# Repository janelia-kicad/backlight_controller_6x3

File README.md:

- [Repository Information](#org89e2f96)
  - [Description](#org01946da)
- [Images](#org5e6b005)
- [Schematic](#org50048ed)
- [Gerbers](#org1f83db4)
- [Bill of Materials](#org4e1d2f2)
  - [PCB Parts](#org0365191)
  - [Supplemental Parts](#org1217ce1)
  - [Vendor Parts Lists](#orge2d2bad)
- [Supplemental Documentation](#org1794ae5)
  - [Assembly Instructions](#orgcad51c4)
- [Manufacturing Archive](#orgdf269ab)

# Repository Information

-   **Name:** backlight\_controller\_6x3
-   **Version:** 1.0
-   **License:** Open-Source Hardware
-   **URL:** <https://github.com/janelia-kicad/backlight_controller_6x3>
-   **Author:** Peter Polidoro
-   **Email:** peter@polidoro.io

## Description

This board controls up to four Smart Vision backlights with IR and visible channels plus additional high and low power channel outputs.

# Images

# Schematic

[./schematic/backlight\_controller\_6x3.pdf](./schematic/backlight_controller_6x3.pdf)

# Gerbers

# Bill of Materials

## PCB Parts

| Item | Reference(s)                                                | Quantity | Manufacturer Part Number | Description                                                       |
|---- |----------------------------------------------------------- |-------- |------------------------ |----------------------------------------------------------------- |
| 1    | C1 C2                                                       | 2        | C2012X5R1V106M085AC      | CAP CER 10UF 35V X5R                                              |
| 2    | C3 C4 C5 C6 C7 C8 C9                                        | 7        | C0805T104K5RAL7800       | CAP CER 0.1UF 50V X7R                                             |
| 3    | D1 D10 D11 D12 D13 D14 D15 D16 D17 D2 D3 D4 D5 D6 D7 D8 D9  | 17       | LTST-C170GKT             | LED GREEN CLEAR SMD                                               |
| 4    | HPS1 HPS2 HPS3 HPS4                                         | 4        | BTS3256DAUMA1            | IC SWITCH SMART LOWSIDE                                           |
| 5    | J1                                                          | 1        | 09551156612741           | CONN D-SUB RCPT 9POS SMD SOLDER                                   |
| 6    | J10 J3 J4 J5 J6 J7 J8 J9                                    | 8        | 1411976                  | CONN FMALE INSERT 5POS SOLDER                                     |
| 7    | J2                                                          | 1        | 09551296812741           | CONN D-SUB PLUG 9POS SMD SOLDER                                   |
| 8    | P1                                                          | 1        | 0039301060               | CONN HEADER 6POS 4.2MM R/A TIN                                    |
| 9    | R1                                                          | 1        | ERJ-6ENF2201V            | RES SMD 2.2K OHM 1% 1/8W                                          |
| 10   | R10 R2 R4 R6 R8                                             | 5        | ERJ-6ENF5901V            | RES SMD 5.9K OHM 1% 1/8W                                          |
| 11   | R11 R13 R15 R17 R19 R20 R21 R22 R23 R24 R25 R26 R3 R5 R7 R9 | 16       | ERJ-6ENF2870V            | RES SMD 287 OHM 1% 1/8W                                           |
| 12   | R12 R14 R16 R18                                             | 4        | ERJ-6ENF75R0V            | RES SMD 75 OHM 1% 1/8W                                            |
| 13   | REG1                                                        | 1        | R-78C5.0-1.0             | CONV DC/DC 1A 5V OUT SIP VERT                                     |
| 14   | SW1 SW2                                                     | 2        | KT11P4SM34LFS            | SWITCH TACTILE SPST-NO 1VA 32V                                    |
| 15   | TEENSY1                                                     | 1        | DEV-14056                | TEENSY 3.5 HDRS K64 EVAL BRD                                      |
| 16   | U1 U2                                                       | 2        | SN74ABT541BDWR           | Buffer Non-Inverting 1 Element 8 Bit per Element Push-Pull Output |
| 17   | U10 U11 U3 U4 U5 U6 U7 U8 U9                                | 9        | NUD3124LT1G              | IC INDCT LOAD DRVR AUTO                                           |
| 18   | U12                                                         | 1        | MAX6817EUT+T             | IC DEBOUNCER SWITCH DUAL                                          |

## Supplemental Parts

| Item | Quantity | Manufacturer Part Number   | Description                    |
|---- |-------- |-------------------------- |------------------------------ |
| 1    | 1        | GST280A24-C6P              | AC/DC DESKTOP ADAPTER 24V 280W |
| 2    | 1        | CORD IEC 320-C13 6FT BLACK | CORD IEC 320-C13 6FT BLACK     |

## Vendor Parts Lists

[./bom/Digi-Key\_parts.csv](./bom/Digi-Key_parts.csv)

[./bom/supplemental\_Digi-Key\_parts.csv](./bom/supplemental_Digi-Key_parts.csv)

# Supplemental Documentation

## Assembly Instructions

-   Solder surface mount and through hole components onto the pcb.

# Manufacturing Archive

Send manufacturing zip file to your favorite PCB manufacturer for fabrication.

[./manufacturing/backlight\_controller\_6x3\_v1.0.zip](./manufacturing/backlight_controller_6x3_v1.0.zip)

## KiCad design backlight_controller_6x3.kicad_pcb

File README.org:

# Created 2019-06-07 Fri 10:33
#+OPTIONS: title:nil author:nil email:nil toc:t |:t ^:nil
* Repository Information

- Name :: backlight_controller_6x3
- Version :: 1.0
- License :: Open-Source Hardware
- URL :: https://github.com/janelia-kicad/backlight_controller_6x3
- Author :: Peter Polidoro
- Email :: peter@polidoro.io

** Description

This board controls up to four Smart Vision backlights with IR and visible
channels plus additional high and low power channel outputs.

* Images

* Schematic

[[file:./schematic/backlight_controller_6x3.pdf][./schematic/backlight_controller_6x3.pdf]]

[[file:./schematic/images/schematic00.png]]

[[file:./schematic/images/schematic01.png]]

[[file:./schematic/images/schematic02.png]]

[[file:./schematic/images/schematic03.png]]

[[file:./schematic/images/schematic04.png]]

[[file:./schematic/images/schematic05.png]]

[[file:./schematic/images/schematic06.png]]

[[file:./schematic/images/schematic07.png]]

[[file:./schematic/images/schematic08.png]]

[[file:./schematic/images/schematic09.png]]

[[file:./schematic/images/schematic10.png]]

[[file:./schematic/images/schematic11.png]]

[[file:./schematic/images/schematic12.png]]

[[file:./schematic/images/schematic13.png]]

[[file:./schematic/images/schematic14.png]]

[[file:./schematic/images/schematic15.png]]

[[file:./schematic/images/schematic16.png]]

[[file:./schematic/images/schematic17.png]]

[[file:./schematic/images/schematic18.png]]

[[file:./schematic/images/schematic19.png]]

[[file:./schematic/images/schematic20.png]]

[[file:./schematic/images/schematic21.png]]

* Gerbers

[[file:./gerbers/images/gerbers00.png]]

[[file:./gerbers/images/gerbers01.png]]

* Bill of Materials

** PCB Parts

| Item | Reference(s)                                                | Quantity | Manufacturer Part Number | Description                                                       |
|------+-------------------------------------------------------------+----------+--------------------------+-------------------------------------------------------------------|
|    1 | C1 C2                                                       |        2 | C2012X5R1V106M085AC      | CAP CER 10UF 35V X5R                                              |
|    2 | C3 C4 C5 C6 C7 C8 C9                                        |        7 | C0805T104K5RAL7800       | CAP CER 0.1UF 50V X7R                                             |
|    3 | D1 D10 D11 D12 D13 D14 D15 D16 D17 D2 D3 D4 D5 D6 D7 D8 D9  |       17 | LTST-C170GKT             | LED GREEN CLEAR SMD                                               |
|    4 | HPS1 HPS2 HPS3 HPS4                                         |        4 | BTS3256DAUMA1            | IC SWITCH SMART LOWSIDE                                           |
|    5 | J1                                                          |        1 | 09551156612741           | CONN D-SUB RCPT 9POS SMD SOLDER                                   |
|    6 | J10 J3 J4 J5 J6 J7 J8 J9                                    |        8 | 1411976                  | CONN FMALE INSERT 5POS SOLDER                                     |
|    7 | J2                                                          |        1 | 09551296812741           | CONN D-SUB PLUG 9POS SMD SOLDER                                   |
|    8 | P1                                                          |        1 | 0039301060               | CONN HEADER 6POS 4.2MM R/A TIN                                    |
|    9 | R1                                                          |        1 | ERJ-6ENF2201V            | RES SMD 2.2K OHM 1% 1/8W                                          |
|   10 | R10 R2 R4 R6 R8                                             |        5 | ERJ-6ENF5901V            | RES SMD 5.9K OHM 1% 1/8W                                          |
|   11 | R11 R13 R15 R17 R19 R20 R21 R22 R23 R24 R25 R26 R3 R5 R7 R9 |       16 | ERJ-6ENF2870V            | RES SMD 287 OHM 1% 1/8W                                           |
|   12 | R12 R14 R16 R18                                             |        4 | ERJ-6ENF75R0V            | RES SMD 75 OHM 1% 1/8W                                            |
|   13 | REG1                                                        |        1 | R-78C5.0-1.0             | CONV DC/DC 1A 5V OUT SIP VERT                                     |
|   14 | SW1 SW2                                                     |        2 | KT11P4SM34LFS            | SWITCH TACTILE SPST-NO 1VA 32V                                    |
|   15 | TEENSY1                                                     |        1 | DEV-14056                | TEENSY 3.5 HDRS K64 EVAL BRD                                      |
|   16 | U1 U2                                                       |        2 | SN74ABT541BDWR           | Buffer Non-Inverting 1 Element 8 Bit per Element Push-Pull Output |
|   17 | U10 U11 U3 U4 U5 U6 U7 U8 U9                                |        9 | NUD3124LT1G              | IC INDCT LOAD DRVR AUTO                                           |
|   18 | U12                                                         |        1 | MAX6817EUT+T             | IC DEBOUNCER SWITCH DUAL                                          |

** Supplemental Parts

| Item | Quantity | Manufacturer Part Number   | Description                    |
|------+----------+----------------------------+--------------------------------|
|    1 |        1 | GST280A24-C6P              | AC/DC DESKTOP ADAPTER 24V 280W |
|    2 |        1 | CORD IEC 320-C13 6FT BLACK | CORD IEC 320-C13 6FT BLACK     |

** Vendor Parts Lists

[[file:./bom/Digi-Key_parts.csv][./bom/Digi-Key_parts.csv]]

[[file:./bom/supplemental_Digi-Key_parts.csv][./bom/supplemental_Digi-Key_parts.csv]]

* Supplemental Documentation

** Assembly Instructions

- Solder surface mount and through hole components onto the pcb.

* Manufacturing Archive

Send manufacturing zip file to your favorite PCB manufacturer for fabrication.

[[file:./manufacturing/backlight_controller_6x3_v1.0.zip][./manufacturing/backlight_controller_6x3_v1.0.zip]]

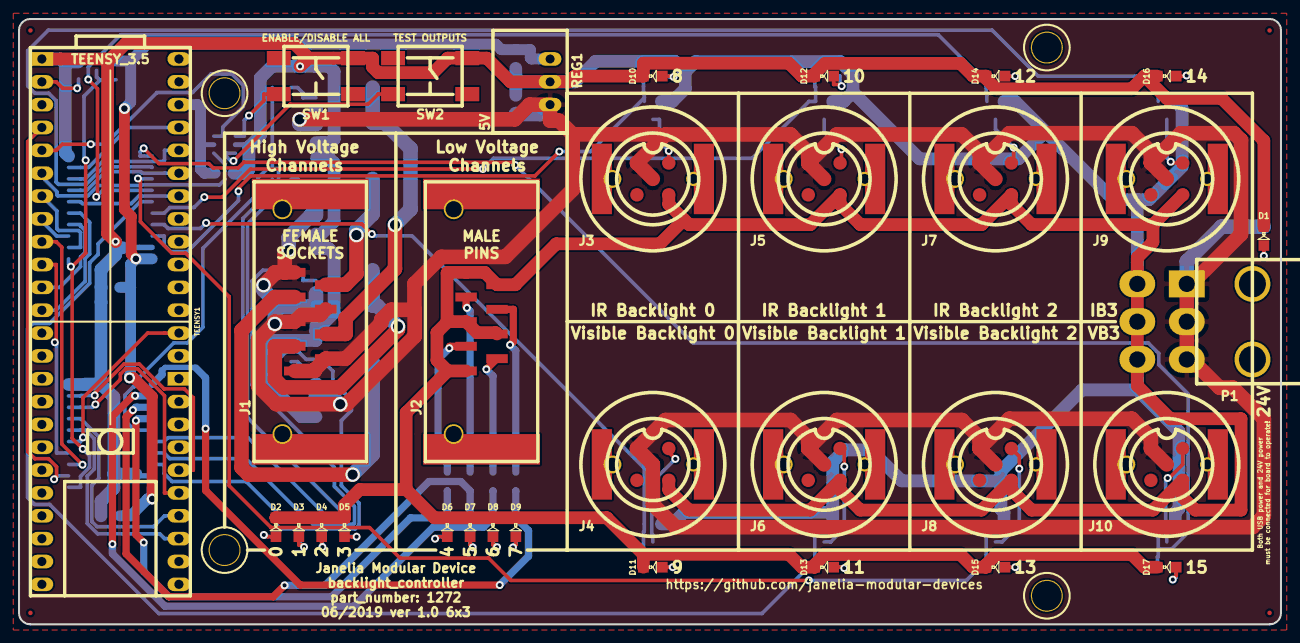
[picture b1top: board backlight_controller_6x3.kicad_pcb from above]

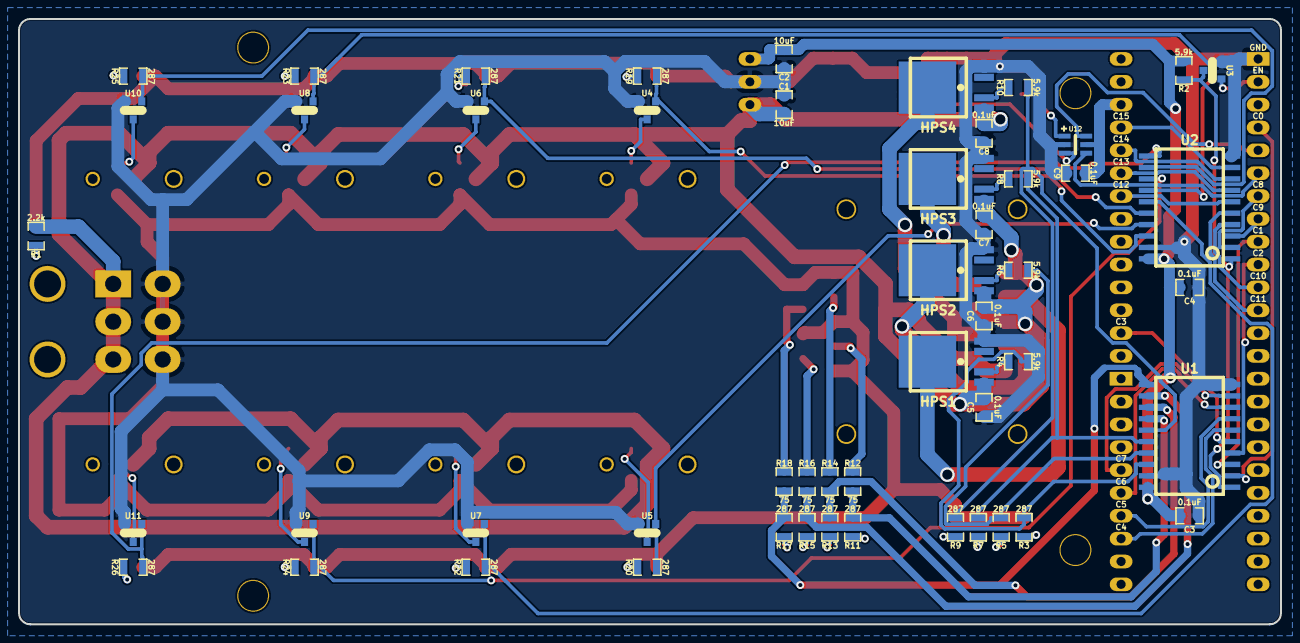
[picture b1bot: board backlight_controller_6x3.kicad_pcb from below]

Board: 2 copper layers, 140.3 x 67.3 mm, 91 parts (51 on the bottom side), 79 nets.

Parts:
C1, C2: 10uF; SM0805
C3, C4, C5, C6, C7, C8, C9: 0.1uF; SM0805
D1, D2, D3, D4, D5, D6, D7, D8, D9, D10, D11, D12, D13, D14, D15, D16, D17: LED_GRN; LED0805
FID1, FID2, FID3, FID4: FIDUCIAL
HPS1, HPS2, HPS3, HPS4: BTS3256; PG-TO252-5-11
J1: DB9F; DB9F_SMD
J2: DB9M; DB9M_SMD
J3, J4, J5, J6, J7, J8, J9, J10: M12-5-RCPT; M12-5_RCPT_F_SMD
MH1, MH2, MH3, MH4: MOUNTING_HOLE_4-40
P1: MINI_FIT; MINI-FIT-JR_02X03_M_RA
R1: 2.2k; SM0805
R2, R4, R6, R8, R10: 5.9k; SM0805
R3, R5, R7, R9, R11, R13, R15, R17, R19, R20, R21, R22, R23, R24, R25, R26: 287; SM0805
R12, R14, R16, R18: 75; SM0805
REG1: CONV_DC_DC_5V_1A; DC_DC_CONV_R78C
SW1, SW2: VAL**; SWITCH_KT
TEENSY1: TEENSY_3.5; TEENSY_3.5_MIN
U1, U2: SN74ABT541BDWR; SOIC_20
U3, U4, U5, U6, U7, U8, U9, U10, U11: NUD3124; TO-236-3
U12: VAL**; MAX6817

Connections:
+3V3: C9.1, TEENSY1.3V3, U12.5
/CHANNEL_0: TEENSY1.2, U1.2
/CHANNEL_1: TEENSY1.7, U1.3
/CHANNEL_2: TEENSY1.8, U1.4
/CHANNEL_3: TEENSY1.14, U1.5
/CHANNEL_4: TEENSY1.35, U1.6
/CHANNEL_5: TEENSY1.36, U1.7
/CHANNEL_6: TEENSY1.37, U1.8
/CHANNEL_7: TEENSY1.38, U1.9
/CHANNEL_8: TEENSY1.5, U2.2
/CHANNEL_9: TEENSY1.6, U2.3
/CHANNEL_10: TEENSY1.9, U2.4
/CHANNEL_11: TEENSY1.10, U2.5
/CHANNEL_12: TEENSY1.20, U2.6
/CHANNEL_13: TEENSY1.21, U2.7
/CHANNEL_14: TEENSY1.22, U2.8
/CHANNEL_15: TEENSY1.23, U2.9
/ENABLE: TEENSY1.0, U3.1
/backlight_6x3/C_0: R3.1, R4.1, U1.18
/backlight_6x3/C_1: R5.1, R6.1, U1.17
/backlight_6x3/C_2: R7.1, R8.1, U1.16
/backlight_6x3/C_3: R9.1, R10.1, U1.15
/backlight_6x3/C_4: R11.1, R12.1, U1.14
/backlight_6x3/C_5: R13.1, R14.1, U1.13
/backlight_6x3/C_6: R15.1, R16.1, U1.12
/backlight_6x3/C_7: R17.1, R18.1, U1.11
/backlight_6x3/C_8: R19.1, U2.18, U4.1
/backlight_6x3/C_9: R20.1, U2.17, U5.1
/backlight_6x3/C_10: R21.1, U2.16, U6.1
/backlight_6x3/C_11: R22.1, U2.15, U7.1
/backlight_6x3/C_12: R23.1, U2.14, U8.1
/backlight_6x3/C_13: R24.1, U2.13, U9.1
/backlight_6x3/C_14: R25.1, U2.12, U10.1
/backlight_6x3/C_15: R26.1, U2.11, U11.1
/backlight_6x3/backlight_outputs/ir_0/NPN: J3.2, U4.3
/backlight_6x3/backlight_outputs/ir_1/NPN: J5.2, U6.3
/backlight_6x3/backlight_outputs/ir_2/NPN: J7.2, U8.3
/backlight_6x3/backlight_outputs/ir_3/NPN: J9.2, U10.3
/backlight_6x3/backlight_outputs/visible_0/NPN: J4.2, U5.3
/backlight_6x3/backlight_outputs/visible_1/NPN: J6.2, U7.3
/backlight_6x3/backlight_outputs/visible_2/NPN: J8.2, U9.3
/backlight_6x3/backlight_outputs/visible_3/NPN: J10.2, U11.3
/backlight_6x3/high_voltage_outputs/OUTPUT_0: HPS1.6, J1.2
/backlight_6x3/high_voltage_outputs/OUTPUT_1: HPS2.6, J1.4
/backlight_6x3/high_voltage_outputs/OUTPUT_2: HPS3.6, J1.6
/backlight_6x3/high_voltage_outputs/OUTPUT_3: HPS4.6, J1.8
/backlight_6x3/high_voltage_outputs/high_voltage_output_0/FAULT: HPS1.2, R4.2
/backlight_6x3/high_voltage_outputs/high_voltage_output_1/FAULT: HPS2.2, R6.2
/backlight_6x3/high_voltage_outputs/high_voltage_output_2/FAULT: HPS3.2, R8.2
/backlight_6x3/high_voltage_outputs/high_voltage_output_3/FAULT: HPS4.2, R10.2
/backlight_6x3/low_voltage_outputs/OUTPUT_0: J2.2, R12.2
/backlight_6x3/low_voltage_outputs/OUTPUT_1: J2.4, R14.2
/backlight_6x3/low_voltage_outputs/OUTPUT_2: J2.6, R16.2
/backlight_6x3/low_voltage_outputs/OUTPUT_3: J2.8, R18.2
/backlight_6x3/~ENABLE: R2.2, U1.1, U2.1, U3.3
/modular_device_base_6x3_male/BTN_0: SW1.2, U12.1
/modular_device_base_6x3_male/BTN_0_D: TEENSY1.3, U12.6
/modular_device_base_6x3_male/BTN_1: SW2.2, U12.3
/modular_device_base_6x3_male/BTN_1_D: TEENSY1.4, U12.4
GND: C1.2, C2.2, C3.2, C4.2, C5.2, C6.2, C7.2, C8.2, C9.2, D1.2, D2.2, D3.2, D4.2, D5.2, D6.2, D7.2, D8.2, D9.2, D10.2, D11.2, D12.2, D13.2, D14.2, D15.2, D16.2, D17.2, HPS1.5, HPS2.5, HPS3.5, HPS4.5, J2.1, J2.3, J2.5, J2.7, J2.9, J3.3, J4.3, J5.3, J6.3, J7.3, J8.3, J9.3, J10.3, P1.4, P1.5, P1.6, REG1.2, SW1.3, SW2.3, TEENSY1.GND, U1.10, U1.19, U2.10, U2.19, U3.2, U4.2, U5.2, U6.2, U7.2, U8.2, U9.2, U10.2, U11.2, U12.2
unnamed: D1.1, R1.2
unnamed: D2.1, R3.2
unnamed: D3.1, R5.2
unnamed: D4.1, R7.2
unnamed: D5.1, R9.2
unnamed: D6.1, R11.2
unnamed: D7.1, R13.2
unnamed: D8.1, R15.2
unnamed: D9.1, R17.2
unnamed: D10.1, R19.2
unnamed: D11.1, R20.2
unnamed: D12.1, R21.2
unnamed: D13.1, R22.2
unnamed: D14.1, R23.2
unnamed: D15.1, R24.2
unnamed: D16.1, R25.2
unnamed: D17.1, R26.2
VAA: C1.1, C5.1, C6.1, C7.1, C8.1, HPS1.1, HPS2.1, HPS3.1, HPS4.1, J1.1, J1.3, J1.5, J1.7, J1.9, J3.1, J3.5, J4.1, J4.5, J5.1, J5.5, J6.1, J6.5, J7.1, J7.5, J8.1, J8.5, J9.1, J9.5, J10.1, J10.5, P1.1, P1.2, P1.3, R1.1, REG1.1
VEE: C2.1, C3.1, C4.1, R2.1, REG1.3, U1.20, U2.20

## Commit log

2019-06-04 Update version documentation
2019-06-04 Progress towards v1.0
2019-06-05 Add enable pullup resistor
2019-06-06 Prerouting
2019-06-06 Route board
2019-06-07 Route board and generate gerbers
2019-06-07 Update documentation
2021-09-16 Update email address
2021-09-21 Remove ignored files
2022-02-22 Add guix files
2022-02-23 Add guix documentation
